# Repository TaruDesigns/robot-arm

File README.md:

This is a small project aimed at building a 6 DOF robot arm using inexpensive components, and control it through a Raspberry Pi.

# This is a fork
Originally a fork from [Stawo's Robot Arm](https://github.com/stawo/robot-arm), I decided to use an Arduino Nano as an I2C  ADC as I already had some available. This project  used the AD1015 ADC, and I thought of using an MCP3008 instead, but at the time of writing, an Arduino is just as cheap and slightly more convenient as it's sold on a board with easy to connect headers.

# Table of Contents
- [This is a fork](#this-is-a-fork)
- [Table of Contents](#table-of-contents)
- [BOM](#bom)
- [Power Supply considerations](#power-supply-considerations)
- [Some Theory](#some-theory)
  - [Controlling Servo Motors](#controlling-servo-motors)
  - [Servo motor feedback](#servo-motor-feedback)
- [Raspberry Pi configuration](#raspberry-pi-configuration)
  - [Raspberry Pi set up](#raspberry-pi-set-up)
  - [Controlling servo motors with Raspberry Pi and the PWM Driver PCA9685](#controlling-servo-motors-with-raspberry-pi-and-the-pwm-driver-pca9685)
  - [Simple GUI](#simple-gui)
  - [Reading the feedback from servo motors with Raspberry Pi](#reading-the-feedback-from-servo-motors-with-raspberry-pi)
  - [Using output enable to manually bring robots to position and learn those positions.](#using-output-enable-to-manually-bring-robots-to-position-and-learn-those-positions)
  - [Arduino Code](#arduino-code)
  - [Inverse Kinematics](#inverse-kinematics)

# BOM
List of components used:
* Raspberry Pi 3 Model B+
* 16GB Micro SD card
* Robot Arm mechanical kit (AliExpress, see the picture for reference as there are many sellers)
* 6x Servo Motors (4x MG996R + 2x Carson CS-3. Ideally they should all be the same model but I had the Carson available)
* 5V 5A Switching Power Supply
* PCA9685 16 Channel 12 Bit PMW Servo Driver [Wiki](http://wiki.sunfounder.cc/index.php?title=PCA9685_16_Channel_12_Bit_PWM_Servo_Driver). There are many clones available.
* Servo Extension Cables
* female-female Dupont jumper wire cable
* Other wiring as needed
* (TODO) Enclosure for all boards and connectors
* Breakout/Connection board

Tools:
* Multimeter
* Electric screwdriver
* Monitor/Keyboard/Mouse/Wi-Fi adapter/SD Adapter for Micro SD for the Raspberry Pi

#  Power Supply considerations
This circuit needs 3 sources of power for each of the 3 main components:
* The Raspberry Pi
* The 6 Servo Motors
* The Arduino/ADC

You might be able to power everything straight from the 5V pin on the Raspberry, but that's a bit risky. The main reason to have different power supplies is that the servos can draw a significant amount of current (especially under load), which might either exceed the RPi 5V pin output or cause significant other issues (brownouts and voltage drops leading to servos misbehaving). From quick tests, I found that the servos can draw around 300mA for a standard movement, and almost twice that if they get stalled or are under significant load. Since we have 6 servos we can easily reach over 2A during some movements, hence the need to separate the power supplies (the RPi will draw about 500mA, possibly more if we add lots of processing in the background)

. I want to build this with all the electronics in a single panel attached to the robot base, with a single DC Barrel 12V input. Therefore, the  power supply consists of:

- One 12V DC power supply. Since the LM2596 converter has a variable input of 6-40V, you might even get away with an 18V laptop power supply
- An LM2596 board with a USB connector that will power the raspberry pi
- Another LM2596 board with a standard screw terminal that will power the servos.
- The arduino will be powered by the Raspberry Pi 5V pin.

|**NOTE**|
|--------|
|The servo motors have to be physically modified in order to read the internal potentiometer. If you use the MG996r, it's the middle pad out of the 3 in a row you can see closest to the wall. [This video](https://www.youtube.com/watch?v=w7qRs6tvxlM) is for a different model of servo but it shows the process 

# Some Theory
Before moving on, it is necessary to understand how the various elements work, especially parts like servo motors, in order to avoid problems (i.e., avoid burning stuff like me due to too much excitement and not knowing how things work!).

## Controlling Servo Motors
A servo motor is usually controllable through PWM (Pulse Width Modulation). Specifically, its arm position depends on the width (or length) of the pulse applied to it.
A PWM signal encodes a ratio. The ratio of on to off is needed to get all the information; on alone is not enough. 
As a concrete example, PWM might be running at a frequency of 200Hz (or a period of 5ms). A 50% of maximum power signal (also known as Duty Cycle) would be on for 2.5ms, and off for 2.5ms. 
Change the frequency to 1000Hz, and hence the period becomes 1ms. The 50% duty cycle would now be 0.5ms on, and 0.5ms off. That PWM signal still encodes the same 50% power information.

Usually, servos can rotate between 0 and 180°. So we have to adjust the pulse length in between. A length of 1.5ms (7.5% duty cycle) thus gives an angle of 90°. And all at precisely 50 times per second (50Hz).
This diagram summarizes how a servo motor is controlled through PWM:

In my case I use the Lewan Soul LD-27MG, which has the following specs:
* working voltage: 6-7.4 V
* min working current: 1 A
* angle: between 0° and 270°
* Pulse Period: 20ms
  thus Frequency: 50Hz
* Pulse Width Range: between 0.5ms and 2.5ms
  thus Duty Cycle: between 2.5% and 12.5%

Conversion table:
Angle   | Pulse Width (ms) | Duty Cycle (%)
------- | ---------------- | --------------
0°      | 0.5              | 2.5
45°     | 0.8333           | 4.1666
90°     | 1.1666           | 5.8333
135°    | 1.5              | 7.5
180°    | 1.8333           | 9.1666
225°    | 2.1666           | 10.8333
270°    | 2.5              | 12.5

Links:
* https://www.teachmemicro.com/raspberry-pi-pwm-servo-tutorial/
* https://tutorials-raspberrypi.com/raspberry-pi-servo-motor-control/

## Servo motor feedback
Normal servo motors do not provide a feedback to the control board (in our case, the Raspberry Pi).
They simply take the PWM generated and do their best to fulfill the "request".

For our robot arm this is not ideal, because the arm could get stuck while doing a movement (for example, we try to push the arm against the table), and this leads to a stall of the servo motor.
Stalling a servo motor will damage it and the control board, as it will increase the current load (see https://electronics.stackexchange.com/questions/274721/how-does-blocking-a-servo-dc-motor-break-it).

Especially in my setup, once the PCA9685 control board sends the PWM signal to the servo motor, there is no way to stop the PWM signal or turn off the servo, and the board will burn out (it happened to me) if the servo stalls.

To understand if a servo motor is in stall (or, alternatively, is operating correctly), we need a feedback from it.
We can achieve this by tapping the potentiometer inside the servo motor, and read the measured voltage.

After modifying the servo motors, we have an extra pin that will output a voltage directly related to the position. This voltage varies for each servo model:
- MG996r seems to go between 0.7V and 2.9V approximately
- CS-3 goes lower, between 0.6V and about 1.8V

This

**Modifying Servos**

Links:
* https://www.youtube.com/watch?v=w7qRs6tvxlM
* https://learn.adafruit.com/analog-feedback-servos/using-feedback
* https://electronics.stackexchange.com/questions/214761/how-to-measure-servo-potentiometer

# Raspberry Pi configuration

I'm running the Raspberry Pi using Raspbian. For the pinout, there's this excellent website: [RPI pinout](https://pinout.xyz/)

## Raspberry Pi set up
To be able to control servo motor through the PCA9685 controller, we need to perform the following steps:
1. Activate the I2C interface in the Raspberry
    * run the command
    ``sudo raspi-config``
    * go to “Interfaces”, select “I2C”, select “Yes”
2. Configuring Raspberry Pi for I2C.
    * Install the following packages:
    ``sudo apt-get install python-smbus``
    ``sudo apt-get install i2c-tools``
    * Add the following lines to ``/etc/modules``:
    ``i2c-dev``
    ``i2c-bcm2708``
    * Reboot the Pi
3. Check that the PCA9685 controller is properly connected and it's set to its default address:
  ``sudo i2cdetect -y 1``
  It should show up at 0x40 (binary 1000000) as follows:
  
4. Connect the PCA9685 controller as in the diagram
5. [optional] Create/activate the Python environment of your choice
6. Install the library https://github.com/adafruit/Adafruit_Python_PCA9685 by running the command:
  ``sudo pip install adafruit-pca9685``

Links:
* https://learn.adafruit.com/adafruit-16-channel-servo-driver-with-raspberry-pi/configuring-your-pi-for-i2c
* https://learn.adafruit.com/adafruit-16-channel-servo-driver-with-raspberry-pi/using-the-adafruit-library

## Controlling servo motors with Raspberry Pi and the PWM Driver PCA9685
**[TO DO]**

## Simple GUI
**[TO DO]**

## Reading the feedback from servo motors with Raspberry Pi
**[TO DO]**

## Using output enable to manually bring robots to position and learn those positions.
**[TO DO]**

## Arduino Code
**[TO DO]**

## Inverse Kinematics
**[TO DO]**

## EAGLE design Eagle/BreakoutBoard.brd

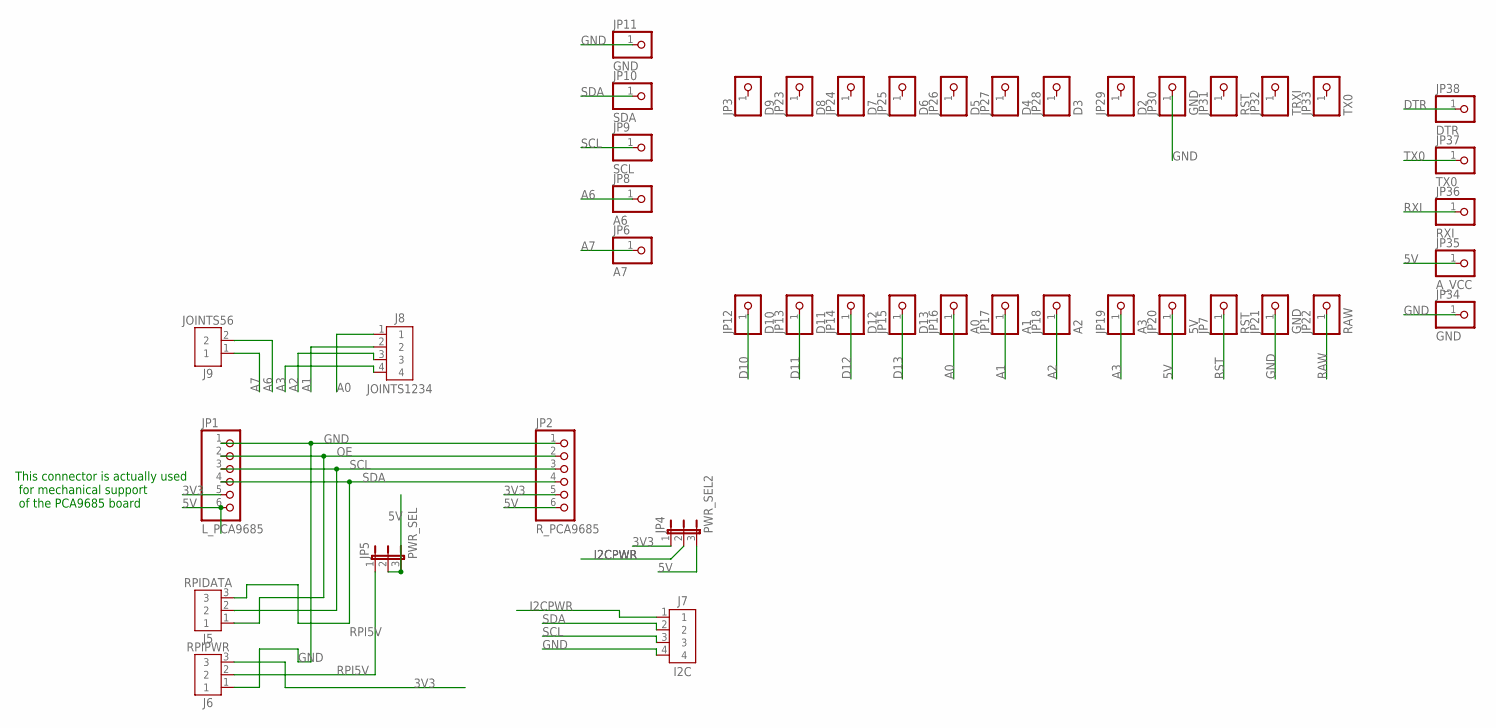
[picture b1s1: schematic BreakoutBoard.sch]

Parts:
J5: RPIDATA; B3B-XH-A
J6: RPIPWR; B3B-XH-A
J7: I2C; B4B-XH-A
J8: JOINTS1234; B4B-XH-A
J9: JOINTS56; B2B-XH-A
JP1: L_PCA9685; 1X06
JP2: R_PCA9685; 1X06
JP3: D9; 1X01
JP4: PWR_SEL2; JP2
JP5: PWR_SEL; JP2
JP6: A7; 1X01
JP7, JP31: RST; 1X01
JP8: A6; 1X01
JP9: SCL; 1X01
JP10: SDA; 1X01
JP11, JP21, JP30, JP34: GND; 1X01
JP12: D10; 1X01
JP13: D11; 1X01
JP14: D12; 1X01
JP15: D13; 1X01
JP16: A0; 1X01
JP17: A1; 1X01
JP18: A2; 1X01
JP19: A3; 1X01
JP20: 5V; 1X01
JP22: RAW; 1X01
JP23: D8; 1X01
JP24: D7; 1X01
JP25: D6; 1X01
JP26: D5; 1X01
JP27: D4; 1X01
JP28: D3; 1X01
JP29: D2; 1X01
JP32: TRXI; 1X01
JP33, JP37: TX0; 1X01
JP35: A_VCC; 1X01
JP36: RXI; 1X01
JP38: DTR; 1X01

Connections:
3V3: J6.3, JP1.5, JP2.5, JP4.1
5V: JP1.6, JP2.6, JP4.3, JP5.2, JP5.3, JP20.1, JP35.1
A0: J8.1, JP16.1
A1: J8.2, JP17.1
A2: J8.3, JP18.1
A3: J8.4, JP19.1
A6: J9.2, JP8.1
A7: J9.1, JP6.1
D10: JP12.1
D11: JP13.1
D12: JP14.1
D13: JP15.1
DTR: JP38.1
GND: J6.1, J7.4, JP1.1, JP2.1, JP11.1, JP21.1, JP30.1, JP34.1
I2CPWR: J7.1, JP4.2
OE: J5.1, JP1.2, JP2.2
RAW: JP22.1
RPI5V: J6.2, JP5.1
RST: JP7.1
RXI: JP36.1
SCL: J5.2, J7.3, JP1.3, JP2.3, JP9.1
SDA: J5.3, J7.2, JP1.4, JP2.4, JP10.1
TX0: JP37.1

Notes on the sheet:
This connector is actually used for mechanical support of the PCA9685 board

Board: 2 copper layers, 43 parts (0 on the bottom side), 14 nets, no tracks yet.

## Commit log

2022-04-17 Changed readme and updated requirements Added arduino code (NEEDS TESTING)
2022-04-23 Fixed hanging issue on arduino ADC. TODO: Even when tied to GND, it will send a "128" (2^7),
2022-04-24 FIXED Arduino ADC first value being wrong by adding leading/trailing byte Added RPI I2C test file to read values from Arduino
2022-05-01 Added Arduino ADC class (needs testing)
2022-05-01 Moved robot servo class to its own file Changed references to ADS1x15 to Arduino
2022-05-15 Started making a breakout board
2022-05-16 Routed board
2022-05-26 Added breakout board Added servo bracket renderings and dimensions
2022-06-09 Done some refactoring and readjusting
2022-06-12 More untested refactoring. It will all get rebased eventually
2022-07-16 Fixed some errors, need more fixes for calibration and movement
